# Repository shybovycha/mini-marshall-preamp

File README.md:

# Marshall JCM800 Micro preamp

*Original schematic:*

*Modified schematic:*

*Prototype:*

*PCB:*

[*Knob:*](https://www.thingiverse.com/thing:4881405/)

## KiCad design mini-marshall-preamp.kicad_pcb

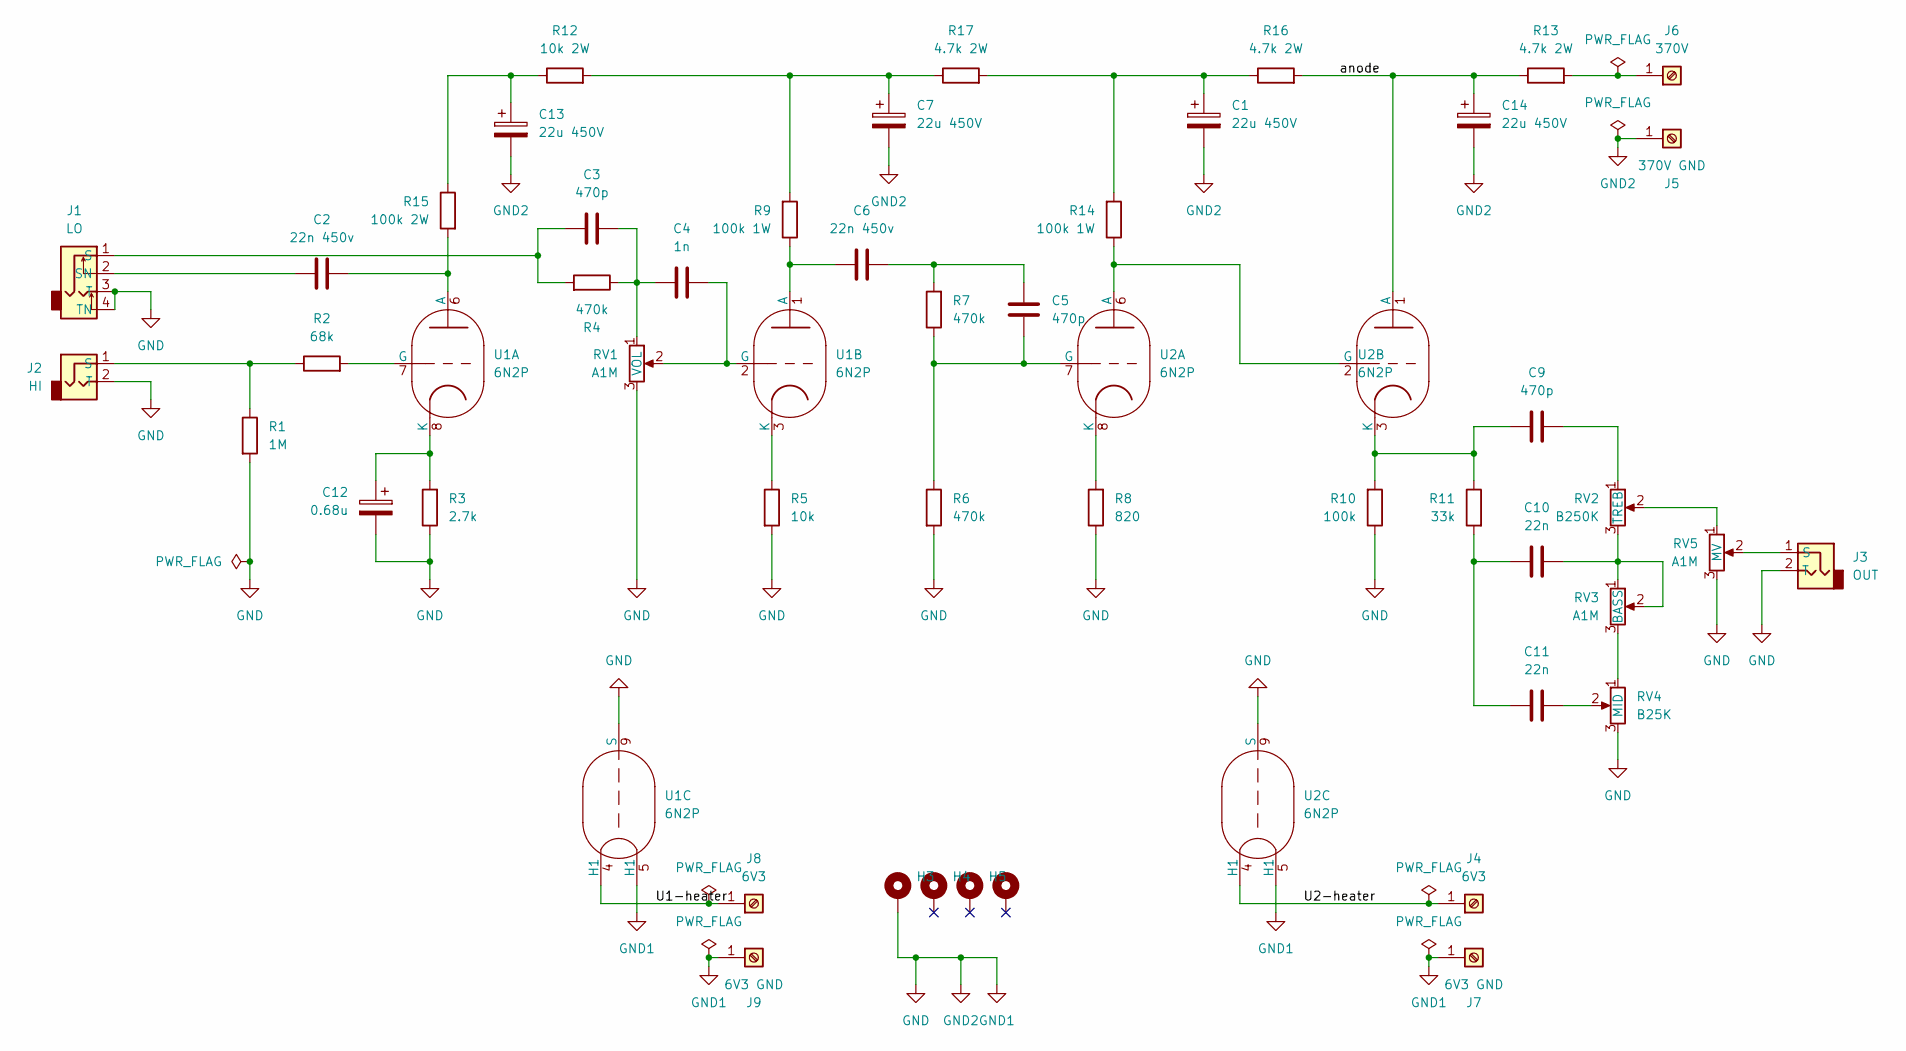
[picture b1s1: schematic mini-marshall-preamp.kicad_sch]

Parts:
C1, C7, C13, C14: 22u 450V; CP_Radial_D13.0mm_P7.50mm
C2: 22n 450v; C_Rect_L11.5mm_W5.1mm_P10.00mm_MKT
C3, C5: 470p; C_Rect_L7.0mm_W2.5mm_P5.00mm
C4: 1n; C_Rect_L7.0mm_W2.5mm_P5.00mm
C6: 22n 450v; C_Rect_L11.5mm_W5.0mm_P10.00mm_MKT
C9: 470p; C_Rect_L9.0mm_W2.5mm_P7.50mm_MKT
C10, C11: 22n; C_Rect_L9.0mm_W2.5mm_P7.50mm_MKT
C12: 0.68u; C_Rect_L9.0mm_W4.2mm_P7.50mm_MKT
H3: MountingHole_Pad; MountingHole_3.2mm_M3_Pad
H4, H5, H6: MountingHole_Pad; MountingHole_3.2mm_M3
J1: LO; SolderWire-1sqmm_1x04_P7.8mm_D1.4mm_OD3.9mm
J2: HI; SolderWire-1sqmm_1x02_P7.8mm_D1.4mm_OD3.9mm
J3: OUT; SolderWire-1sqmm_1x02_P7.8mm_D1.4mm_OD3.9mm
J4, J8: 6V3; SolderWire-1sqmm_1x01_D1.4mm_OD2.7mm
J5: 370V GND; SolderWire-1sqmm_1x01_D1.4mm_OD2.7mm
J6: 370V; SolderWire-1sqmm_1x01_D1.4mm_OD2.7mm
J7, J9: 6V3 GND; SolderWire-1sqmm_1x01_D1.4mm_OD2.7mm
R1: 1M; R_Axial_DIN0207_L6.3mm_D2.5mm_P10.16mm_Horizontal
R2: 68k; R_Axial_DIN0207_L6.3mm_D2.5mm_P10.16mm_Horizontal
R3: 2.7k; R_Axial_DIN0207_L6.3mm_D2.5mm_P10.16mm_Horizontal
R4, R6, R7: 470k; R_Axial_DIN0207_L6.3mm_D2.5mm_P10.16mm_Horizontal
R5: 10k; R_Axial_DIN0207_L6.3mm_D2.5mm_P10.16mm_Horizontal
R8: 820; R_Axial_DIN0207_L6.3mm_D2.5mm_P10.16mm_Horizontal
R9, R14: 100k 1W; R_Axial_DIN0516_L15.5mm_D5.0mm_P20.32mm_Horizontal
R10: 100k; R_Axial_DIN0207_L6.3mm_D2.5mm_P10.16mm_Horizontal
R11: 33k; R_Axial_DIN0516_L15.5mm_D5.0mm_P20.32mm_Horizontal
R12: 10k 2W; R_Axial_DIN0516_L15.5mm_D5.0mm_P20.32mm_Horizontal
R13, R16, R17: 4.7k 2W; R_Axial_DIN0516_L15.5mm_D5.0mm_P20.32mm_Horizontal
R15: 100k 2W; R_Axial_DIN0516_L15.5mm_D5.0mm_P20.32mm_Horizontal
RV1, RV3, RV5: A1M; SolderWire-1sqmm_1x03_P7.8mm_D1.4mm_OD3.9mm
RV2: B250K; SolderWire-1sqmm_1x03_P7.8mm_D1.4mm_OD3.9mm
RV4: B25K; SolderWire-1sqmm_1x03_P7.8mm_D1.4mm_OD3.9mm
U1, U2: 6N2P; Valve_6N2P-3

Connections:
/U1-heater: J8.1, U1.4 (H1)
/U2-heater: J4.1, U2.4 (H1)
/anode: C14.1, R13.1, R16.2, U2.1 (A)
GND: C1.2, C7.2, C12.2, C13.2, C14.2, H3.1, J1.3 (T), J1.4 (TN), J2.2 (T), J3.2 (T), J5.1, J7.1, J9.1, R1.2, R3.1, R5.2, R6.2, R8.1, R10.1, RV1.3, RV4.3, RV5.3, U1.5 (H1), U1.9 (S), U2.5 (H1), U2.9 (S)
unnamed: C1.1, R14.2, R16.1, R17.2
unnamed: C3.2, C4.1, R4.1, RV1.1
unnamed: C5.2, C6.1, R7.2
unnamed: C7.1, R9.2, R12.2, R17.1
unnamed: C9.1, RV2.1
unnamed: C10.1, RV2.3, RV3.1, RV3.2
unnamed: C10.2, C11.2, R11.2
unnamed: C11.1, RV4.2
unnamed: C13.1, R12.1, R15.1
unnamed: C3.1, J1.1 (S), R4.2
unnamed: C2.1, J1.2 (SN)
unnamed: J2.1 (S), R1.1, R2.1
unnamed: J3.1 (S), RV5.2
unnamed: J6.1, R13.2
unnamed: RV2.2, RV5.1
unnamed: RV3.3, RV4.1
unnamed: C2.2, R15.2, U1.6 (A)
unnamed: R2.2, U1.7 (G)
unnamed: C12.1, R3.2, U1.8 (K)
unnamed: C6.2, R9.1, U1.1 (A)
unnamed: C4.2, RV1.2, U1.2 (G)
unnamed: R5.1, U1.3 (K)
unnamed: R14.1, U2.2 (G), U2.6 (A)
unnamed: C5.1, R6.1, R7.1, U2.7 (G)
unnamed: R8.2, U2.8 (K)
unnamed: C9.2, R10.2, R11.1, U2.3 (K)

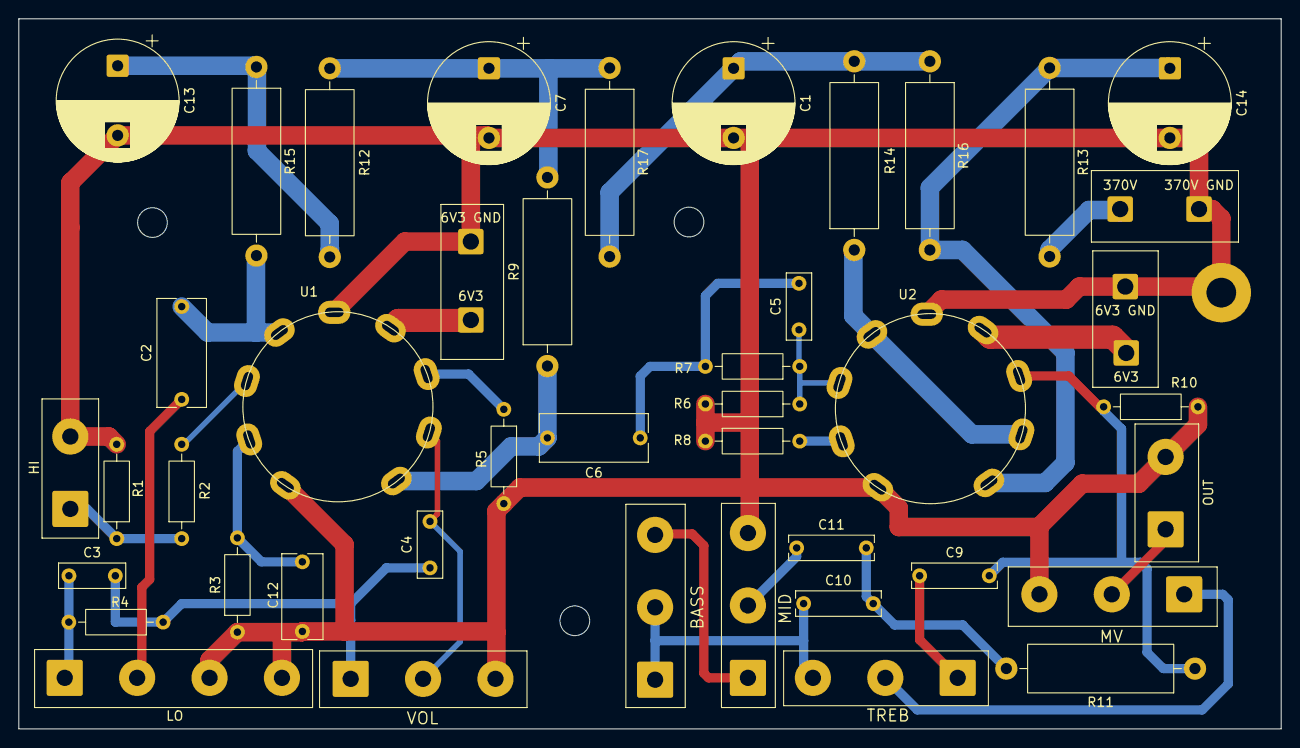
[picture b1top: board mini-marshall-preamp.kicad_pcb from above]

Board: 2 copper layers, 136.0 x 76.5 mm, 50 parts (0 on the bottom side), 30 nets.

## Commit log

2026-03-06 Fixed the schematic
2026-03-06 Swap units A & B of the tubes for consistency
2026-03-10 Update schematic with extra caps and proper input jacks
2026-03-10 Start PCB
2026-03-10 Use external connection footprints for pots and jacks
2026-03-10 First PCB layout
2026-03-10 Layout attempt
2026-03-11 Restart laying out board for size optimization
2026-03-11 Nice layout
2026-03-11 Add mounting holes
2026-03-11 Screenshots
2026-03-11 Tune clearances
2026-03-11 Track widths and prettifying
2026-03-11 Add readme and few photos
2026-03-28 Upgrade to KiCad 10
